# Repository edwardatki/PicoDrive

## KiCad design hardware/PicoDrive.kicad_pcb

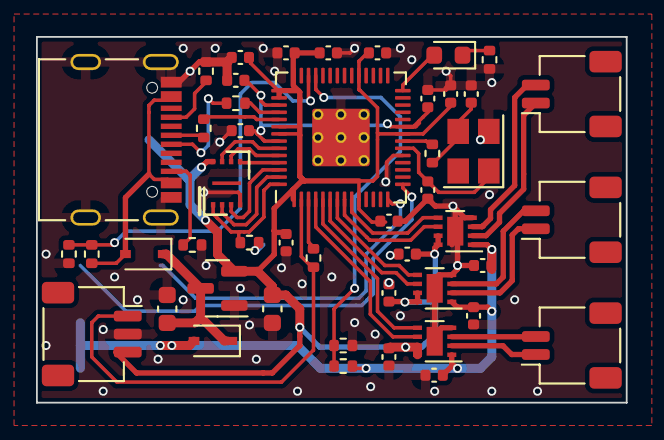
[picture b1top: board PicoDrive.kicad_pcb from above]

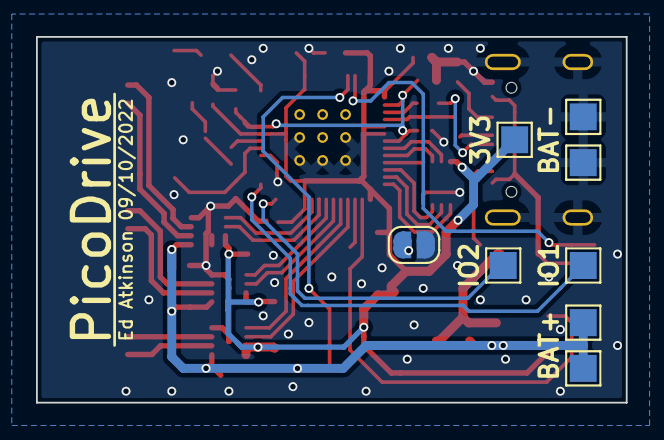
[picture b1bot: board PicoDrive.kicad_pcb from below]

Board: 2 copper layers, 32.8 x 20.3 mm, 55 parts (8 on the bottom side), 42 nets.

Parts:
C1, C3: 10u; C_0603_1608Metric
C2, C8: 1u; C_0402_1005Metric
C4, C7, C9, C10, C11, C12, C13, C14, C15, C16, C17, C18, C19, C20: 100n; C_0402_1005Metric
C5, C6: 27p; C_0402_1005Metric
D1, D2: 1N5819; D_SOD-323
D3: LED GREEN; LED_0603_1608Metric
J1: M1; JST_SH_SM02B-SRSS-TB_1x02-1MP_P1.00mm_Horizontal
J2: M2; JST_SH_SM02B-SRSS-TB_1x02-1MP_P1.00mm_Horizontal
J3: M3; JST_SH_SM02B-SRSS-TB_1x02-1MP_P1.00mm_Horizontal
J4: RECEIVER; JST_SH_SM03B-SRSS-TB_1x03-1MP_P1.00mm_Horizontal
JP1: Jumper_2_Open; SolderJumper-2_P1.3mm_Open_RoundedPad1.0x1.5mm
P1: USB_C_Plug_USB2.0; USB_C_Receptacle_Palconn_UTC16-G
R1, R2: 5K1; R_0402_1005Metric
R3, R4, R9, R11: 1K; R_0402_1005Metric
R5, R6: 27R4; R_0402_1005Metric
R7: 1K2; R_0402_1005Metric
R8, R10: 3K3; R_0402_1005Metric
R12: 220R; R_0402_1005Metric
TP1, TP2: BAT+; TestPoint_Pad_1.5x1.5mm
TP3, TP4: BAT-; TestPoint_Pad_1.5x1.5mm
TP5: PWM1; TestPoint_Pad_1.5x1.5mm
TP6: PWM2; TestPoint_Pad_1.5x1.5mm
TP7: 3V3; TestPoint_Pad_1.5x1.5mm
U1: W25Q32JVSS; 8-USON
U2: XC6206PxxxMR; SOT-23
U3: RP2040; RP2040-QFN-56
U4, U5, U6: DRV8837; WSON-8-1EP_2x2mm_P0.5mm_EP0.9x1.6mm
Y1: Crystal_GND2; Crystal_SMD_3225-4Pin_3.2x2.5mm

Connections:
+1V1: C2.1, C4.1, C7.1, U3.23 (DVDD), U3.45 (VREG_VOUT), U3.50 (DVDD)
+3V3: C3.1, C8.1, C9.1, C10.1, C11.1, C12.1, C13.1, C14.1, C15.1, C16.1, C17.1, J4.3, TP7.1, U1.8 (VCC), U2.2 (VO), U3.1 (IOVDD), U3.10 (IOVDD), U3.22 (IOVDD), U3.33 (IOVDD), U3.42 (IOVDD), U3.43 (ADC_AVDD), U3.44 (VREG_IN), U3.48 (USB_VDD), U3.49 (IOVDD), U4.7 (~SLEEP), U4.8 (VCC), U5.7 (~SLEEP), U5.8 (VCC), U6.7 (~SLEEP), U6.8 (VCC)
+BATT: C18.1, C19.1, C20.1, D2.2 (A), R10.1, TP1.1, TP2.1, U4.1 (VM), U5.1 (VM), U6.1 (VM)
/IBUS: J4.1, R7.1, U3.2 (GPIO0)
/IO_1: TP5.1, U3.15 (GPIO12)
/IO_2: TP6.1, U3.14 (GPIO11)
/M1+: J1.1, U4.2 (OUT1)
/M1-: J1.2, U4.3 (OUT2)
/M1A: U3.8 (GPIO6), U4.6 (IN1)
/M1B: U3.9 (GPIO7), U4.5 (IN2)
/M2+: J2.1, U5.2 (OUT1)
/M2-: J2.2, U5.3 (OUT2)
/M2A: U3.6 (GPIO4), U5.6 (IN1)
/M2B: U3.7 (GPIO5), U5.5 (IN2)
/M3+: J3.1, U6.2 (OUT1)
/M3-: J3.2, U6.3 (OUT2)
/M3A: U3.4 (GPIO2), U6.6 (IN1)
/M3B: U3.5 (GPIO3), U6.5 (IN2)
/VBUS: D1.2 (A), P1.A4 (VBUS), P1.A9 (VBUS), P1.B4 (VBUS), P1.B9 (VBUS), R8.1
GND: C1.2, C2.2, C3.2, C4.2, C5.2, C6.2, C7.2, C8.2, C9.2, C10.2, C11.2, C12.2, C13.2, C14.2, C15.2, C16.2, C17.2, C18.2, C19.2, C20.2, J4.2, JP1.2 (B), P1.A1 (GND), P1.A12 (GND), P1.B1 (GND), P1.B12 (GND), P1.S1 (SHIELD), R1.1, R2.1, R9.2, R11.2, R12.2, TP3.1, TP4.1, U1.4 (GND), U2.1 (GND), U3.19 (TESTEN), U3.57 (GND), U4.4 (GND), U4.9 (GND), U5.4 (GND), U5.9 (GND), U6.4 (GND), U6.9 (GND), Y1.2
unnamed: C1.1, D1.1 (K), D2.1 (K), U2.3 (VI)
unnamed: C5.1, U3.20 (XIN), Y1.1
unnamed: C6.1, R4.2, Y1.3
unnamed: D3.1 (K), R12.1
unnamed: D3.2 (A), U3.28 (GPIO17)
unnamed: JP1.1 (A), R3.2
unnamed: P1.A5 (CC), R1.2
unnamed: P1.B5 (VCONN), R2.2
unnamed: R4.1, U3.21 (XOUT)
unnamed: R5.2, U3.47 (USB_DP)
unnamed: R6.2, U3.46 (USB_DM)
unnamed: R7.2, U3.3 (GPIO1)
unnamed: R8.2, R9.1, U3.40 (GPIO28_ADC2)
unnamed: R10.2, R11.1, U3.39 (GPIO27_ADC1)
QSPI_D0: U1.5 (DI(IO0)), U3.53 (QSPI_SD0)
QSPI_D1: U1.2 (DO(IO1)), U3.55 (QSPI_SD1)
QSPI_D2: U1.3 (IO2), U3.54 (QSPI_SD2)
QSPI_D3: U1.7 (IO3), U3.51 (QSPI_SD3)
QSPI_SCLK: U1.6 (CLK), U3.52 (QSPI_SCLK)
QSPI_SS: R3.1, U1.1 (~CS), U3.56 (QSPI_SS)
USB_DM: P1.A7 (D-), R6.1
USB_DP: P1.A6 (D+), R5.1

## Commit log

2022-10-09 As ordered
2022-10-20 Started firmware
    Also fixed an error on the PCB layout
2022-10-24 More firmware and some schematic updates
2022-11-07 Failsafe fixing
